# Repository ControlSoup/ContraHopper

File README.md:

# Quick Overview [No Longer Maintained as of 07-12-23]
The ContraHopper is a small rotor craft using two counter rotating propellers and jet vanes to maintain attitude and altitude. This project is a personal project with unnecessary constraints to mimic the control of VTVL rockets. 

This repository is not intended for collaborative use at this time.

## Formal Introduction
ContraHopper is a project that stems from my personal interest in the design, control, and operation of rocket-powered landers. Landers operate under the final stage of a planetary mission and serve the purpose of transferring the payload to the surface of your target planetary body. Over the years there has been a considerable number of terrestrial landers that attempt to help test technology associated with landing on other planets and in my opinion, these vehicles are the most interesting flying things to leave the surface of the earth. 

Ultimately I have had to scrap this project due to professional goals, I am keeping this up for reference on my future topics.

Figure 1: Left to Right: Pixel (Armadillo), Xodiac (Masten), Delta Clipper (NASA), Mighty Eagle NASA)

Vehicles like this give me incredible joy. My goal with the project is create a low budget version that is
capable of many of the same things that terrestrial landers do, all from scratch as much as I can help to do.

## Constraints and Milestones

### The constraints are as follows:
  - Minimum 1.5 minutes of flight time
  - Affordable at the Hobby scale
  - Dynamics of the vehicle a close to a rocket as possible at this scale

### The milestones are as follows:
  - Document design decisions and rational
  - Document initial expected vehicle capabilities based on design decisions
  - Full characterization of vehicle using simulation
  - Completion of a 10s hover and landing
  - Completion of a 30s hover and landing with complete position control within a reasonable    tolerance
  - Completion of a 1min flight with a translation in both height and distance, demonstrating position,
    velocity, attitude and trajectory control within a reasonable tolerance

## Folder Structure
Each folder acts as a container for a part of the project, these will eventually hold all files that I used to design an operate ContraHopper for better or for worse. Currently every folder is a work in progress, many contain their own README.md with an overview and and a list of TO-DOs.

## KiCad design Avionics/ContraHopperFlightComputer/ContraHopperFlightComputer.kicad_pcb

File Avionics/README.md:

# Avionics
This folder contains all the files used to create the flight computer used on the ContraHopper project. 

## Data_Sheets
Refrence data sheets for integrated circuits and sensors that interface with the flight computer

## FlightBread
Contains the KiCad project, schematic and layout of the flight computer.

FlightBread 0.1 is complete:
### ToDo
- Fix mounting holes
- FS-IA6 outline is backwards
- LM358 opamp is the wrong scale

## FlightBread_Footprints
Contains custom KiCad Footprint

## FlightBread_Symbols
Contains custom KiCad Symbols

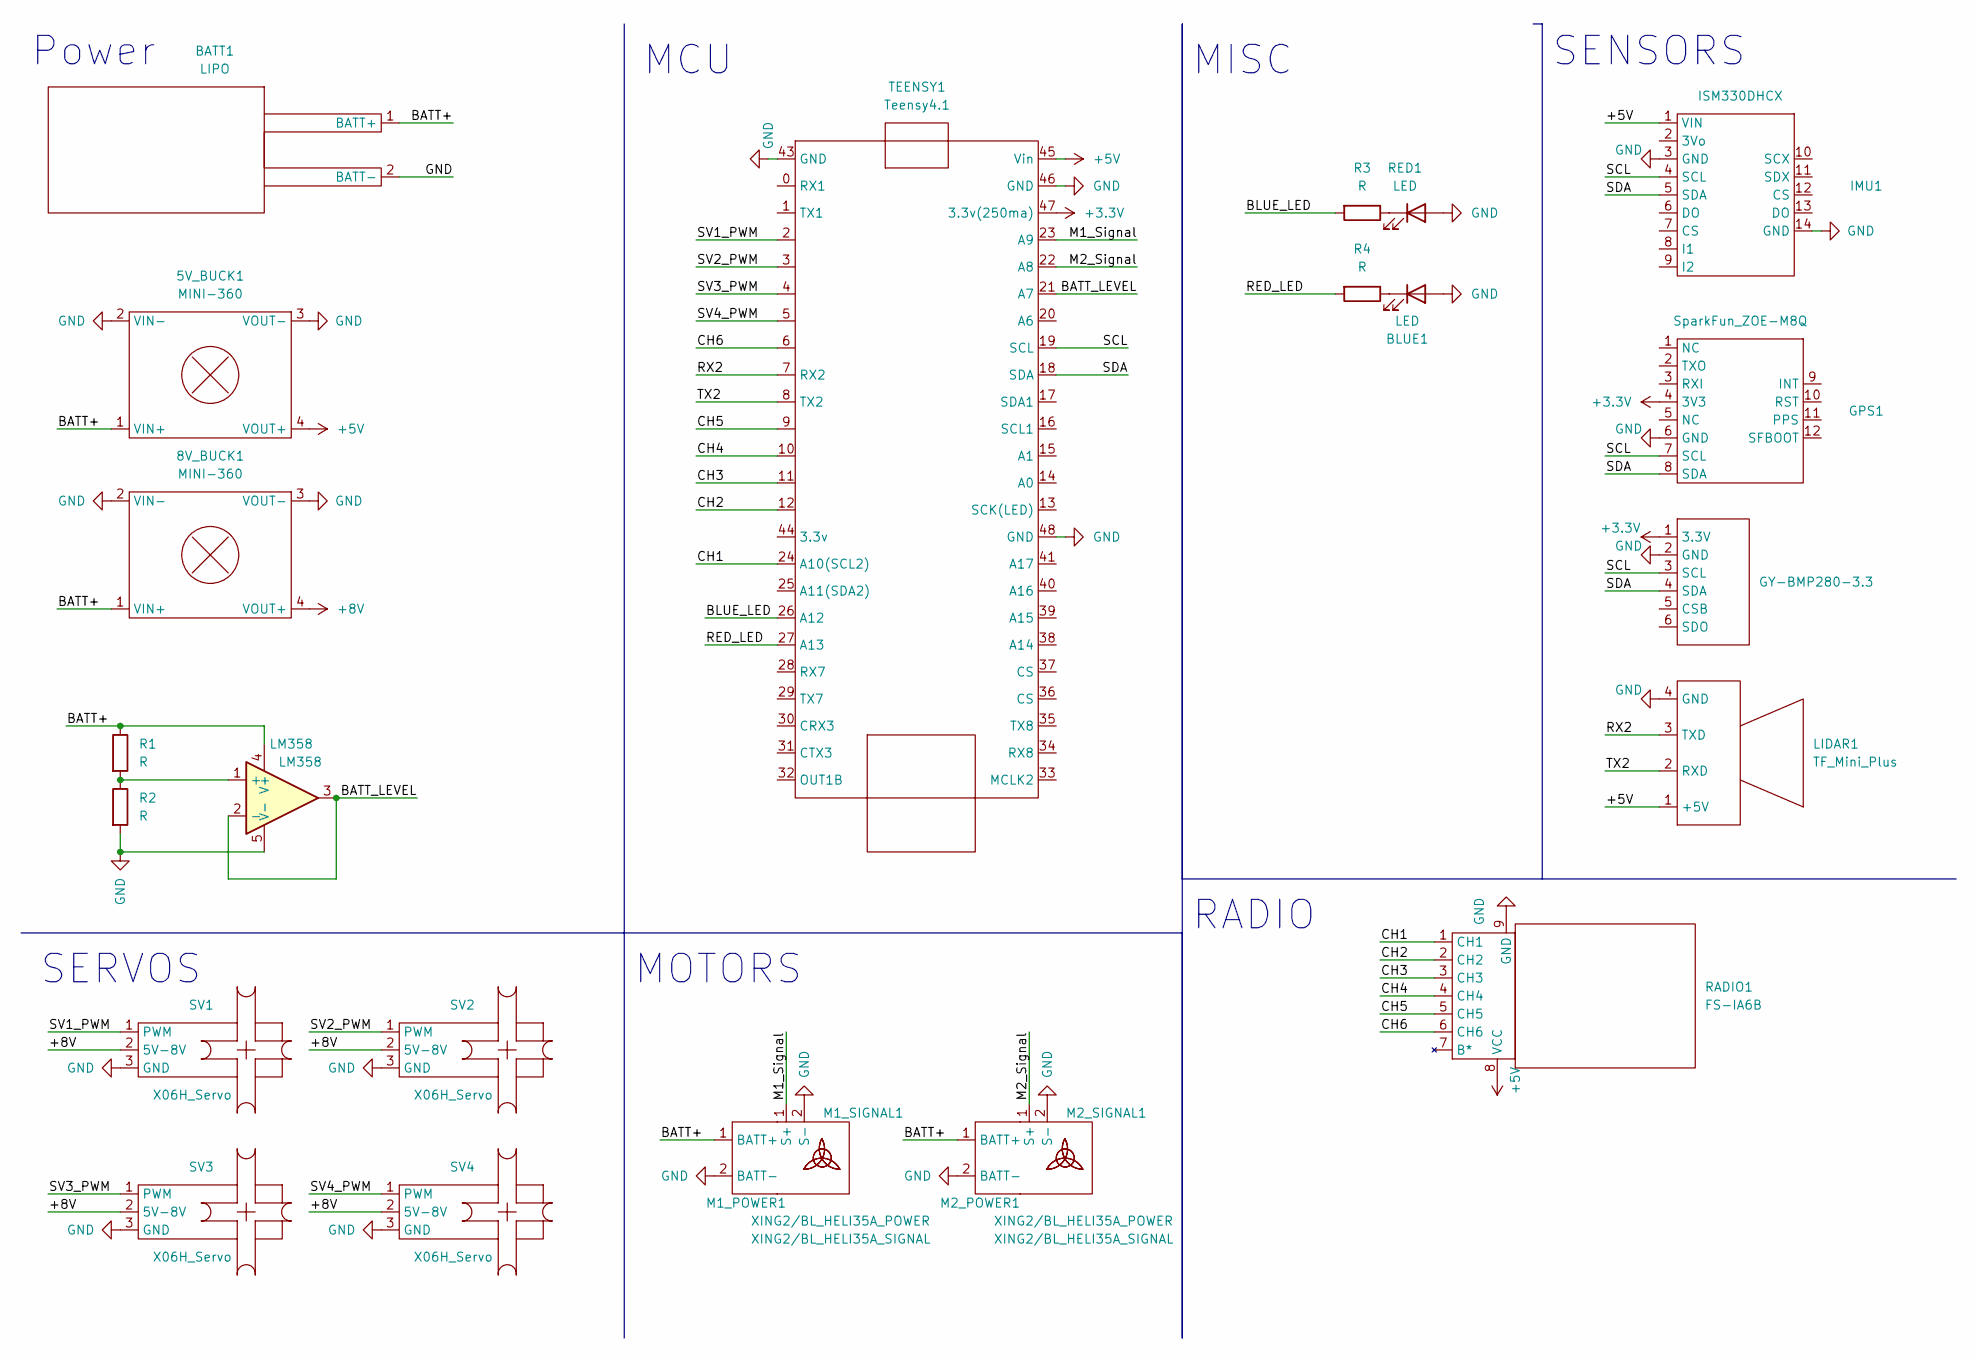
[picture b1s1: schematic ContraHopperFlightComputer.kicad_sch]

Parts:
5V_BUCK1, 8V_BUCK1: MINI-360; MINI_360
BARO1: GY-BMP280-3.3; JST_XH_4pin
BATT1: LIPO; XT60_MOUNT
BLUE1: LED
GPS1: SparkFun_ZOE-M8Q; SparkFun_ZOEM8Q
IMU1: ISM330DHCX
LIDAR1: TF_Mini_Plus; JST_XH_4pin
LM358: LM358
M1_POWER1, M2_POWER1: XING2/BL_HELI35A_POWER; ESC_POWER
M1_SIGNAL1, M2_SIGNAL1: XING2/BL_HELI35A_SIGNAL; JST_XH_2pin
R1, R2, R3, R4: R; pinhole_resistor
RADIO1: FS-IA6B
RED1: LED
SV1, SV2, SV3, SV4: X06H_Servo; JST_XH_3pin
TEENSY1: Teensy4.1

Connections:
+3.3V: BARO1.1 (3.3V), GPS1.4 (3V3), TEENSY1.47 (3.3v(250ma))
+5V: 5V_BUCK1.4 (VOUT+), IMU1.1 (VIN), LIDAR1.1 (+5V), RADIO1.8 (VCC), TEENSY1.45 (Vin)
+8V: 8V_BUCK1.4 (VOUT+), SV1.2 (5V-8V), SV2.2 (5V-8V), SV3.2 (5V-8V), SV4.2 (5V-8V)
/BATT+: 5V_BUCK1.1 (VIN+), 8V_BUCK1.1 (VIN+), BATT1.1 (BATT+), LM358.4 (V+), M1_POWER1.1 (BATT+), M2_POWER1.1 (BATT+), R1.1
/BATT_LEVEL: LM358.2 (-), LM358.3, TEENSY1.21 (A7)
/BLUE_LED: R3.2, TEENSY1.26 (A12)
/CH1: RADIO1.1 (CH1), TEENSY1.24 (A10(SCL2))
/CH2: RADIO1.2 (CH2), TEENSY1.12
/CH3: RADIO1.3 (CH3), TEENSY1.11
/CH4: RADIO1.4 (CH4), TEENSY1.10
/CH5: RADIO1.5 (CH5), TEENSY1.9
/CH6: RADIO1.6 (CH6), TEENSY1.6
/M1_Signal: M1_SIGNAL1.1 (S+), TEENSY1.23 (A9)
/M2_Signal: M2_SIGNAL1.1 (S+), TEENSY1.22 (A8)
/RED_LED: R4.2, TEENSY1.27 (A13)
/RX2: LIDAR1.3 (TXD), TEENSY1.7 (RX2)
/SCL: BARO1.3 (SCL), GPS1.7 (SCL), IMU1.4 (SCL), TEENSY1.19 (SCL)
/SDA: BARO1.4 (SDA), GPS1.8 (SDA), IMU1.5 (SDA), TEENSY1.18 (SDA)
/SV1_PWM: SV1.1 (PWM), TEENSY1.2
/SV2_PWM: SV2.1 (PWM), TEENSY1.3
/SV3_PWM: SV3.1 (PWM), TEENSY1.4
/SV4_PWM: SV4.1 (PWM), TEENSY1.5
/TX2: LIDAR1.2 (RXD), TEENSY1.8 (TX2)
GND: 5V_BUCK1.2 (VIN-), 5V_BUCK1.3 (VOUT-), 8V_BUCK1.2 (VIN-), 8V_BUCK1.3 (VOUT-), BARO1.2 (GND), BATT1.2 (BATT-), BLUE1.2 (A), GPS1.6 (GND), IMU1.3 (GND), IMU1.14 (GND), LIDAR1.4 (GND), LM358.5 (V-), M1_POWER1.2 (BATT-), M1_SIGNAL1.2 (S-), M2_POWER1.2 (BATT-), M2_SIGNAL1.2 (S-), R2.2, RADIO1.9 (GND), RED1.2 (A), SV1.3 (GND), SV2.3 (GND), SV3.3 (GND), SV4.3 (GND), TEENSY1.43 (GND), TEENSY1.46 (GND), TEENSY1.48 (GND)
unnamed: BLUE1.1 (K), R4.1
unnamed: LM358.1 (+), R1.2, R2.1
unnamed: R3.1, RED1.1 (K)

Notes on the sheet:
Power
MOTORS
RADIO
MISC
SERVOS
SENSORS
MCU

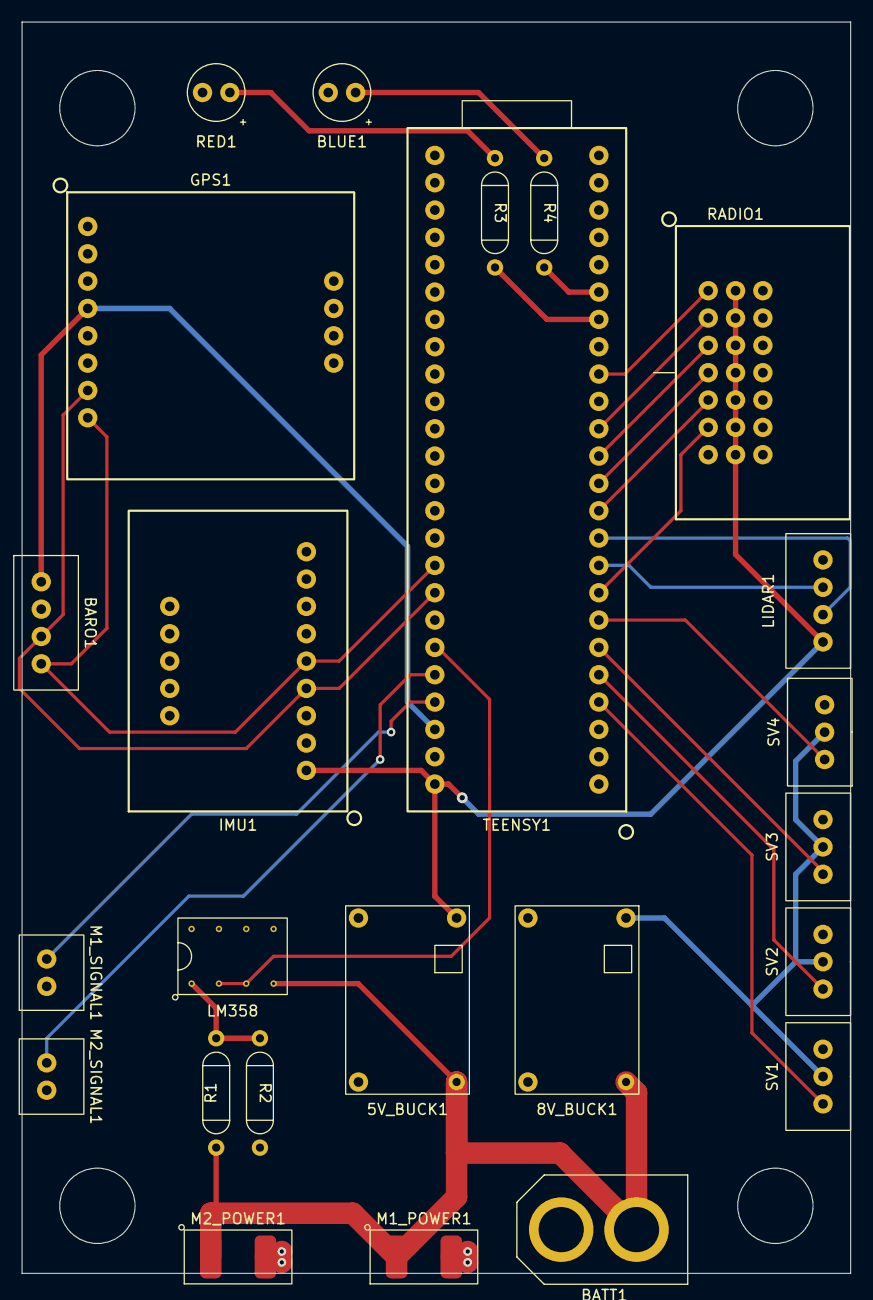
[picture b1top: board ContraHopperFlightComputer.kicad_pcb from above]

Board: 2 copper layers, 77.0 x 116.3 mm, 24 parts (0 on the bottom side), 27 nets.

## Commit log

2022-06-12 BIG CHANGE
2022-06-13 working except dcm
2022-06-14 orthonormalize next
2022-06-24 3rd case still no match
2022-07-12 Progress, but not very directed
2022-07-21 Minor Fixes
2022-07-26 Allocation Update
2022-09-04 Updated File Structure
    File Structures for future
2022-09-05 Files added
    Added the failed impact duration testing, indicates the need for another test stand
2022-09-10 Documentation For Latex
    Documentation Updates
2022-09-11 Master Document, and Landing Leg Completion
2022-09-19 Ready for First Print
    Added some functions to SEF and finished the Tether Truss portion of the Contra Doc
2022-10-02 Grammar Fixes
2022-11-14 Added Flight Software Folder, verified SSH with RASPI
2022-11-19 added some data sheets
2022-11-25 switches to Teensy 4.1, and updating documentation
2022-12-18 switching over to a C version of the simulation
2022-12-18 switched to C for the simulation
2022-12-18 Setup C tasks and linalg dependency
2022-12-18 folder structure
2022-12-20 built a workspace
2022-12-23 playing around with C
2022-12-27 Cleaned up sim, added some basic plotting, but plotting needs improvment
2022-12-27 removed visual studio related files for flight software
2022-12-27 updated Test readme
2022-12-28 Renamed state_vector to state_matrix, added work to Sensors class
2022-12-28 updated formating
2022-12-28 started work on the software sim, currently have not been able to pass a 1d vector back to python
2022-12-28 succesfully passed an array to the flight sim function and back
2022-12-29 switched to a vector format instead of a matrix format, confirmed passing a vector to a C functinos owkrs
2022-12-30 added misc files
2023-01-02 added a start to the multivar kalman, but needed more linear algebra functions) deleted allocation work
2023-01-02 got 3d plotting to work, now does oreintation and position animated
2023-01-02 velocity was not corrected for the body frame
2023-01-02 integration is not working, a 1rad/s for 10s does not result in 10rad
2023-01-02 orthonormalizing a dcm rate is what caused the error
2023-01-03 access error when calling controller function. but format is there
2023-01-03 got position control working in python
2023-01-08 finally found a reliable way to pass double arrays
2023-01-08 updated sensor model
2023-01-08 first pass at a sensor_model
2023-01-08 ajor errors
2023-01-08 sadlt inputs dont work, need to record acceleration in the state..or somthing lol
2023-01-08 first pass a sensor model (kinda sketchy)
2023-01-22 switched over to a basilisk simulation, implemented plotting ect
2023-01-22 udpated readme for archive
2023-01-22 test external force torque functionality
2023-01-30 clean from new desktop
2023-01-30 update for kidcad
2023-01-30 updated kicad files
2023-01-30 kicad fully integrated with git hub
2023-02-20 flight_comptuer_draft_1
2023-02-20 FlightBread_0.1
2023-02-20 Updated general documentation
2023-02-20 readme update
2023-02-25 flight bread and more
2023-02-26 first board print, rushed but I wanna get somthing to start writing the code.....
2023-03-11 added flight bread image
2023-03-12 folder_structure_update
2023-03-13 updated Asoftware with gps and imu, tested on FlightBread, imu works but need antenna for GPS
2024-12-01 re-activation
2024-12-01 updated archive
2024-12-01 gitignore file
